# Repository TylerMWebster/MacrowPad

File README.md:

# MacrowPad
Simple Arduino programmable macro pad

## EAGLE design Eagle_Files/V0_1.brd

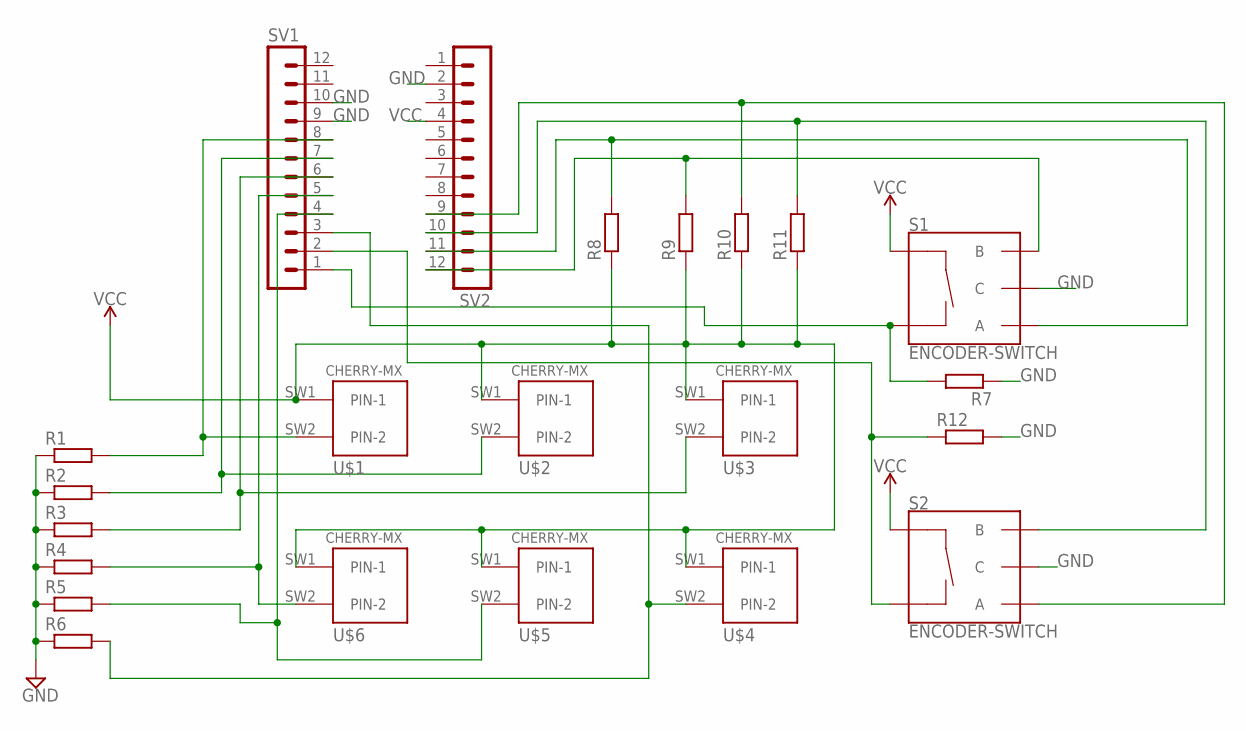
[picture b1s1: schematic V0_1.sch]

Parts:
R1, R2, R3, R4, R5, R6, R7, R8, R9, R10, R11, R12: R-EU_0207/10; 0207/10
S1, S2: ENCODER-SWITCH; ROTARY_ENC_PLAIN
SV1, SV2: MA12-1
U$1, U$2, U$3, U$4, U$5, U$6: CHERRY-MX

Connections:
GND: R1.1, R2.1, R3.1, R4.1, R5.1, R6.1, R7.1, R12.2, S1.C, S2.C, SV1.9, SV1.10, SV2.2
unnamed: R1.2, SV1.8, U$1.SW2 (PIN-2)
unnamed: R2.2, SV1.7, U$2.SW2 (PIN-2)
unnamed: R3.2, SV1.6, U$3.SW2 (PIN-2)
unnamed: R4.2, SV1.5, U$6.SW2 (PIN-2)
unnamed: R5.2, SV1.4, U$5.SW2 (PIN-2)
unnamed: R6.2, SV1.3, U$4.SW2 (PIN-2)
unnamed: R9.2, S1.B, SV2.12
unnamed: R8.2, S1.A, SV2.11
unnamed: R7.2, S1.SW-, SV1.1
unnamed: R11.2, S2.B, SV2.10
unnamed: R10.2, S2.A, SV2.9
unnamed: R12.1, S2.SW-, SV1.2
VCC: R8.1, R9.1, R10.1, R11.1, S1.SW+, S2.SW+, SV2.4, U$1.SW1 (PIN-1), U$2.SW1 (PIN-1), U$3.SW1 (PIN-1), U$4.SW1 (PIN-1), U$5.SW1 (PIN-1), U$6.SW1 (PIN-1)

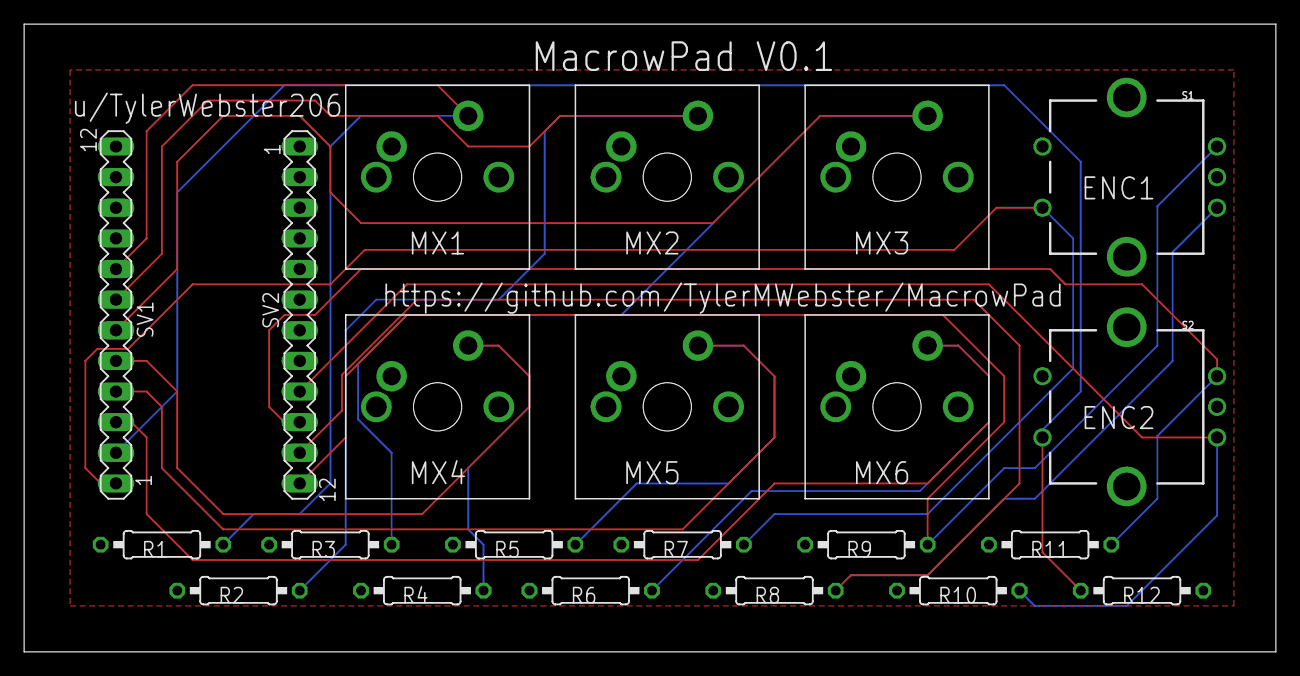
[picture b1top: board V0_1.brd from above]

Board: 2 copper layers, 103.8 x 52.1 mm, 22 parts (0 on the bottom side), 14 nets.

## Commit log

2022-03-01 Silkscreen fix
2022-03-01 Fixed switch spacing
2022-03-01 Version 0_1 final

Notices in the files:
parts and their libraries:
SparkFun-Switches: Licensing: Creative Commons ShareAlike 4.0 International - https://creativecommons.org/licenses/by-sa/4.0
